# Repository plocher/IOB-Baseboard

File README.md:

# IOB-Baseboard
## License: CERN Open Hardware Licence v1.2

IOB Baseboard - wiring termination and I2C / Power bus management

The latest in the evolution of the perfect layout I/O system...
Previous I2C-xxx designs either let to a proliferation of adapters
(current sink, input filters...) and to less than robust mechanical
designs (daughtercards that easily pulled out of their sockets with
cable movement)

This version does 4 things:
 * All wiring is terminated into mechanically stable connection points
 * There are personality adapters to account for the level shifting, buffering and other I/O line adaptions that may be needed
 * While I like having blinking LED lights on every I/O line for debugging, others do not - so there is now a plug-in LED monitor slot for each set of 4x I/O lines
 * A generic I2C Expander plug in footprint.

I have built several board variations for various different I2C
Expander chips to take advantage of unique addressing, I/O levels,
cost, etc - with the only thing changing between boards being the
chip related stuff.  Maintaining and stocking several "slightly
different" board designs gets expensive, both from both inventory
and support perspectives.

V1.0 is a prototype that seeks to validate the basic modular assumptions I'm making.

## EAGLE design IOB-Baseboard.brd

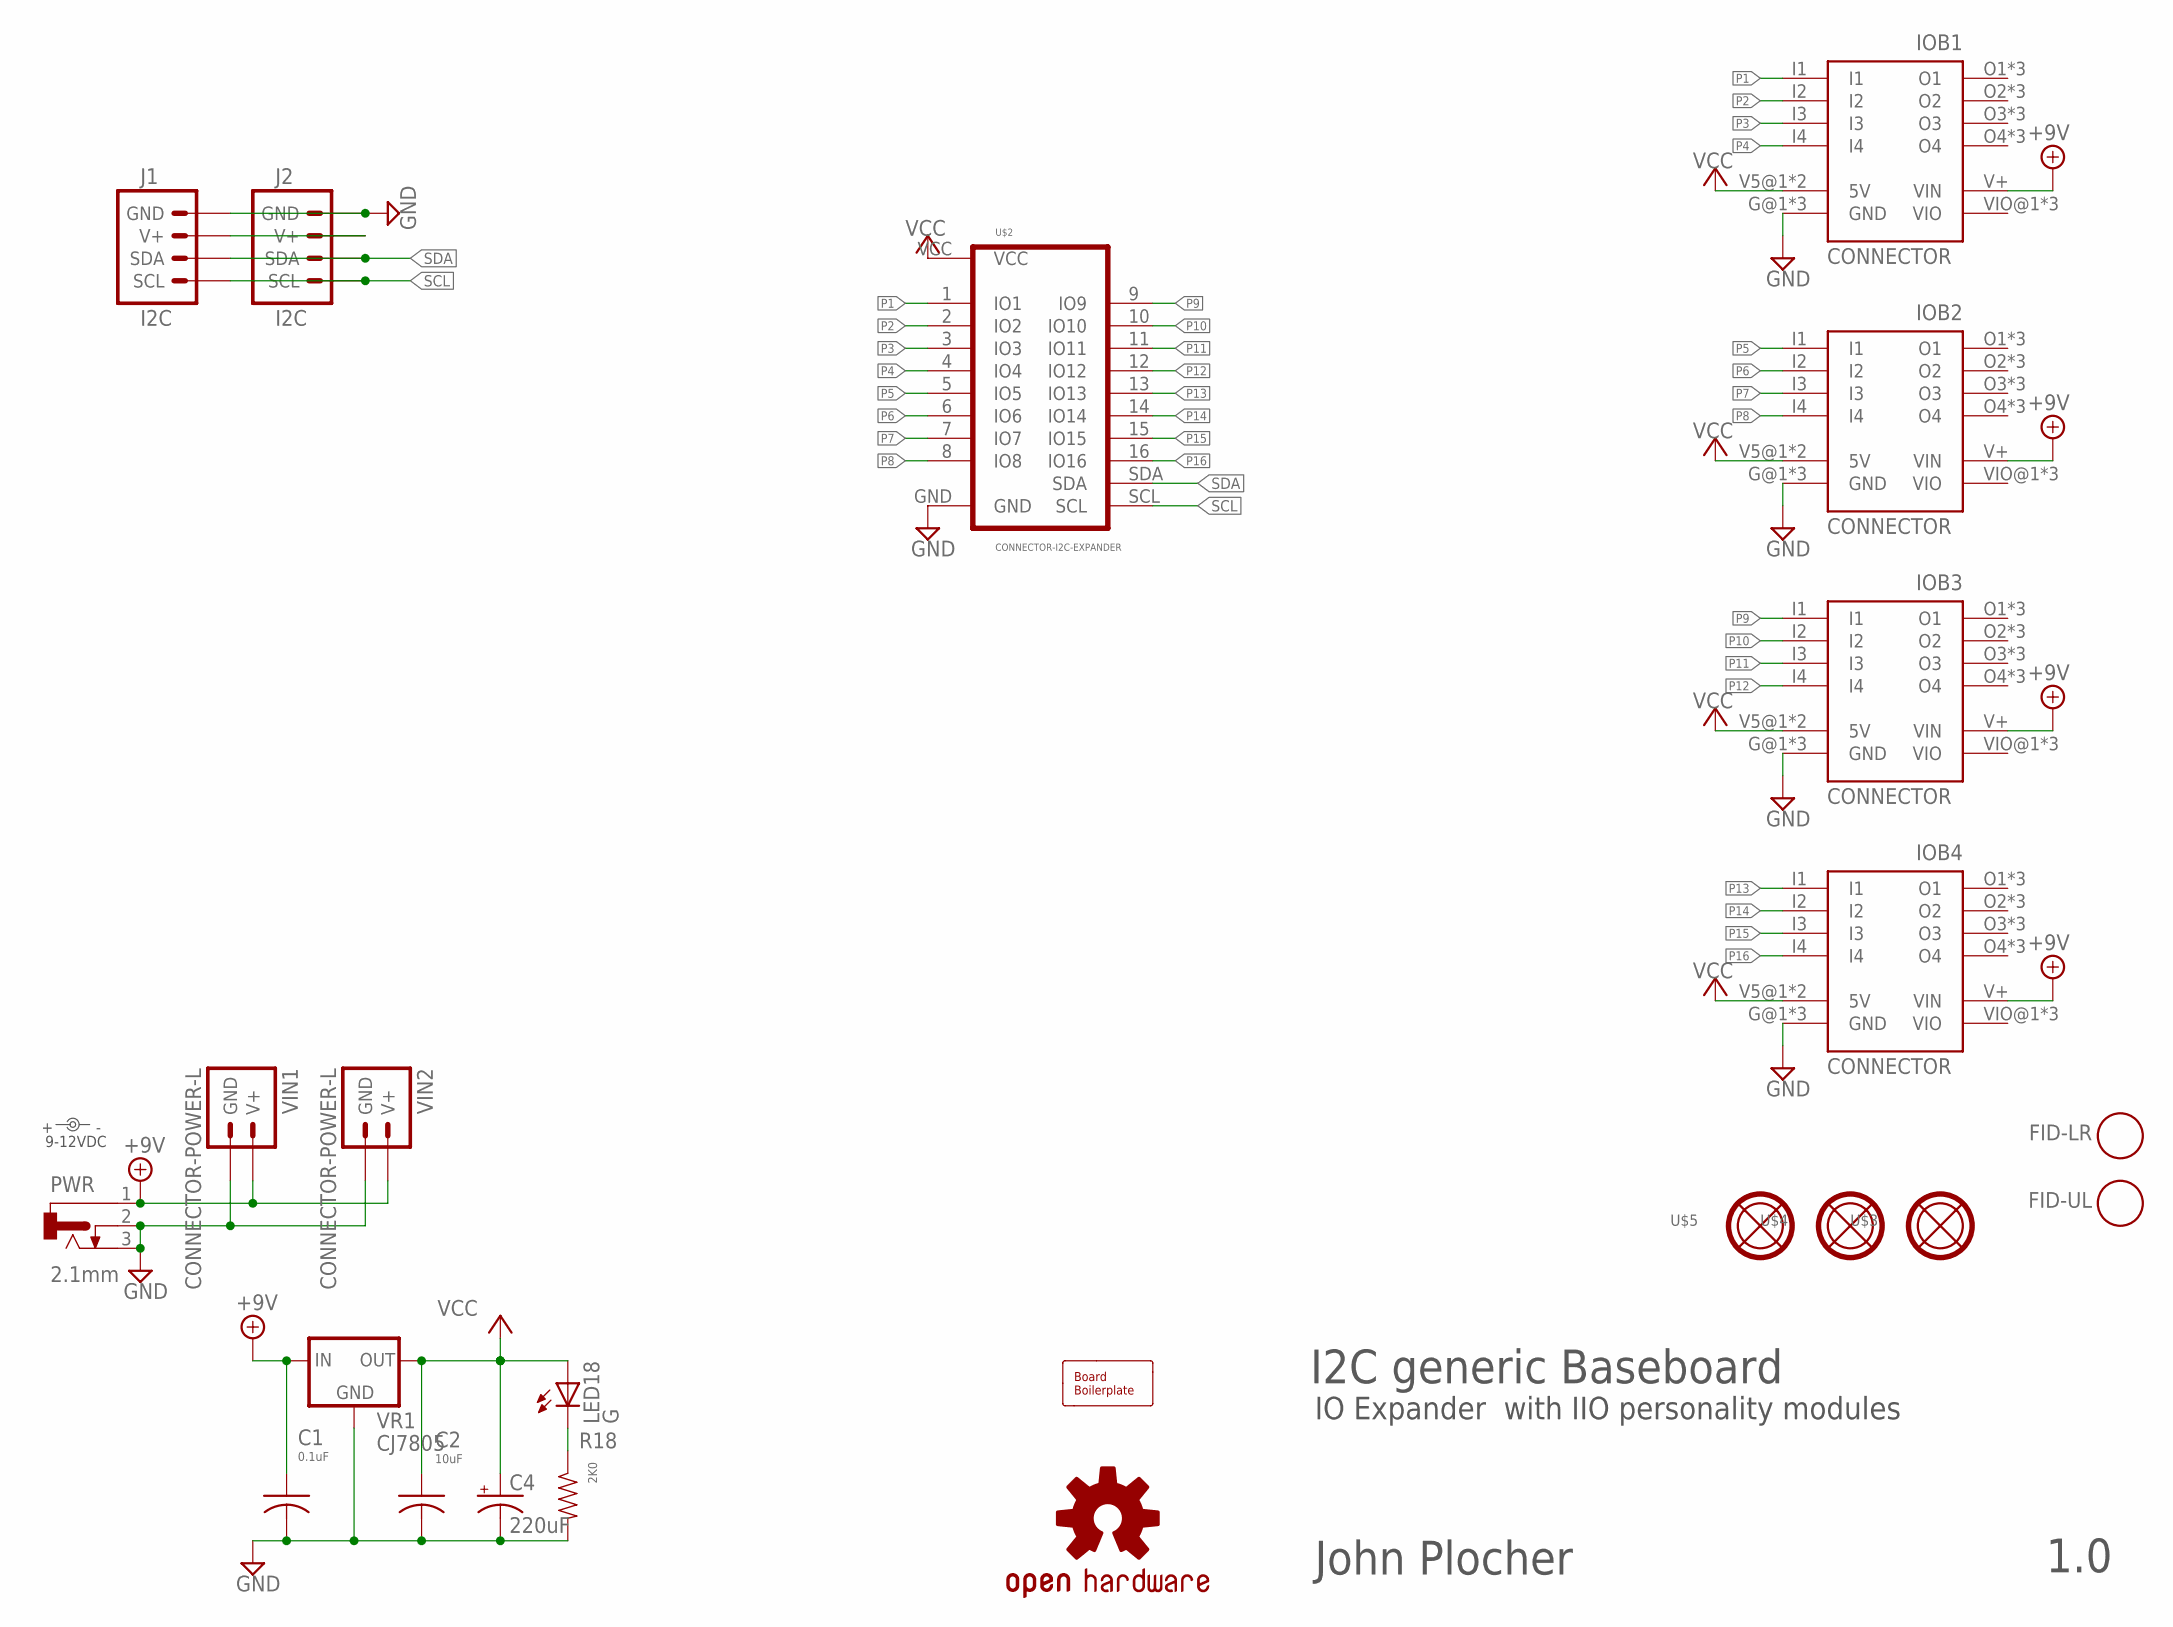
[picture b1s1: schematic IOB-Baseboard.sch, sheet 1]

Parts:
BOARD1: BOARD; BOARD-DINRAIL-3.17IN-IOB
C1: 0.1uF; 0603-CAP
C2: 10uF; 0603-CAP
C4: 220uF; 0810-CAP
FID-LR: FIDUCIAL; FIDUCIAL_1MM
FID-UL: FIDUCIAL; FIDUCIAL_1MM
IOB1, IOB2, IOB3, IOB4: CONNECTOR; IOB-V3-BASE
J1, J2: I2C; I2C-L
LED18: G; 0603-LED
PWR: 2.1mm; DCJ0202
R18: 2K0; 0603-RES
U$1: OSHW; OSHW-LOGO-L
U$2: CONNECTOR-I2C-EXPANDER; I2C-EXPANDER
U$3, U$4, U$5: MOUNTINGHOLE
VIN: 9-12VDC; PWR_LABEL
VIN1, VIN2: CONNECTOR-POWER-L; POWER-R2
VR1: CJ7805; TO-252

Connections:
GND: C1.2, C2.2, C4.-, IOB1.G@1 (GND), IOB1.G@2 (GND), IOB1.GND@3 (GND), IOB2.G@1 (GND), IOB2.G@2 (GND), IOB2.GND@3 (GND), IOB3.G@1 (GND), IOB3.G@2 (GND), IOB3.GND@3 (GND), IOB4.G@1 (GND), IOB4.G@2 (GND), IOB4.GND@3 (GND), J1.GND, J1.GND@1 (GND), J2.GND, J2.GND@1 (GND), PWR.2, PWR.3, R18.2, U$2.GND, VIN1.GND, VIN1.GND@1 (GND), VIN1.GND@2 (GND), VIN1.GND@3 (GND), VIN2.GND, VIN2.GND@1 (GND), VIN2.GND@2 (GND), VIN2.GND@3 (GND), VR1.2 (GND); also elsewhere on the board
unnamed: LED18.C, R18.1
P1: IOB1.I1, U$2.1 (IO1); also elsewhere on the board
P2: IOB1.I2, U$2.2 (IO2); also elsewhere on the board
P3: IOB1.I3, U$2.3 (IO3); also elsewhere on the board
P4: IOB1.I4, U$2.4 (IO4); also elsewhere on the board
P5: IOB2.I1, U$2.5 (IO5); also elsewhere on the board
P6: IOB2.I2, U$2.6 (IO6); also elsewhere on the board
P7: IOB2.I3, U$2.7 (IO7); also elsewhere on the board
P8: IOB2.I4, U$2.8 (IO8); also elsewhere on the board
P9: IOB3.I1, U$2.9 (IO9); also elsewhere on the board
P10: IOB3.I2, U$2.10 (IO10); also elsewhere on the board
P11: IOB3.I3, U$2.11 (IO11); also elsewhere on the board
P12: IOB3.I4, U$2.12 (IO12); also elsewhere on the board
P13: IOB4.I1, U$2.13 (IO13); also elsewhere on the board
P14: IOB4.I2, U$2.14 (IO14); also elsewhere on the board
P15: IOB4.I3, U$2.15 (IO15); also elsewhere on the board
P16: IOB4.I4, U$2.16 (IO16); also elsewhere on the board
SCL: J1.SCL, J1.SCL@1 (SCL), J2.SCL, J2.SCL@1 (SCL), U$2.SCL
SDA: J1.SDA, J1.SDA@1 (SDA), J2.SDA, J2.SDA@1 (SDA), U$2.SDA
V+I2C: J1.V+, J1.V+@1 (V+), J2.V+, J2.V+@1 (V+)
VCC: C2.1, C4.+, IOB1.V5@1 (5V), IOB1.V5@2 (5V), IOB2.V5@1 (5V), IOB2.V5@2 (5V), IOB3.V5@1 (5V), IOB3.V5@2 (5V), IOB4.V5@1 (5V), IOB4.V5@2 (5V), LED18.A, U$2.VCC, VR1.3 (OUT); also elsewhere on the board
VIN: C1.1, IOB1.V+ (VIN), IOB2.V+ (VIN), IOB3.V+ (VIN), IOB4.V+ (VIN), PWR.1, VIN1.V+, VIN1.V+@1 (V+), VIN1.V+@2 (V+), VIN1.V+@3 (V+), VIN2.V+, VIN2.V+@1 (V+), VIN2.V+@2 (V+), VIN2.V+@3 (V+), VR1.1 (IN)

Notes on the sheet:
I2C generic Baseboard
IO Expander with IIO personality modules
John Plocher
1.0

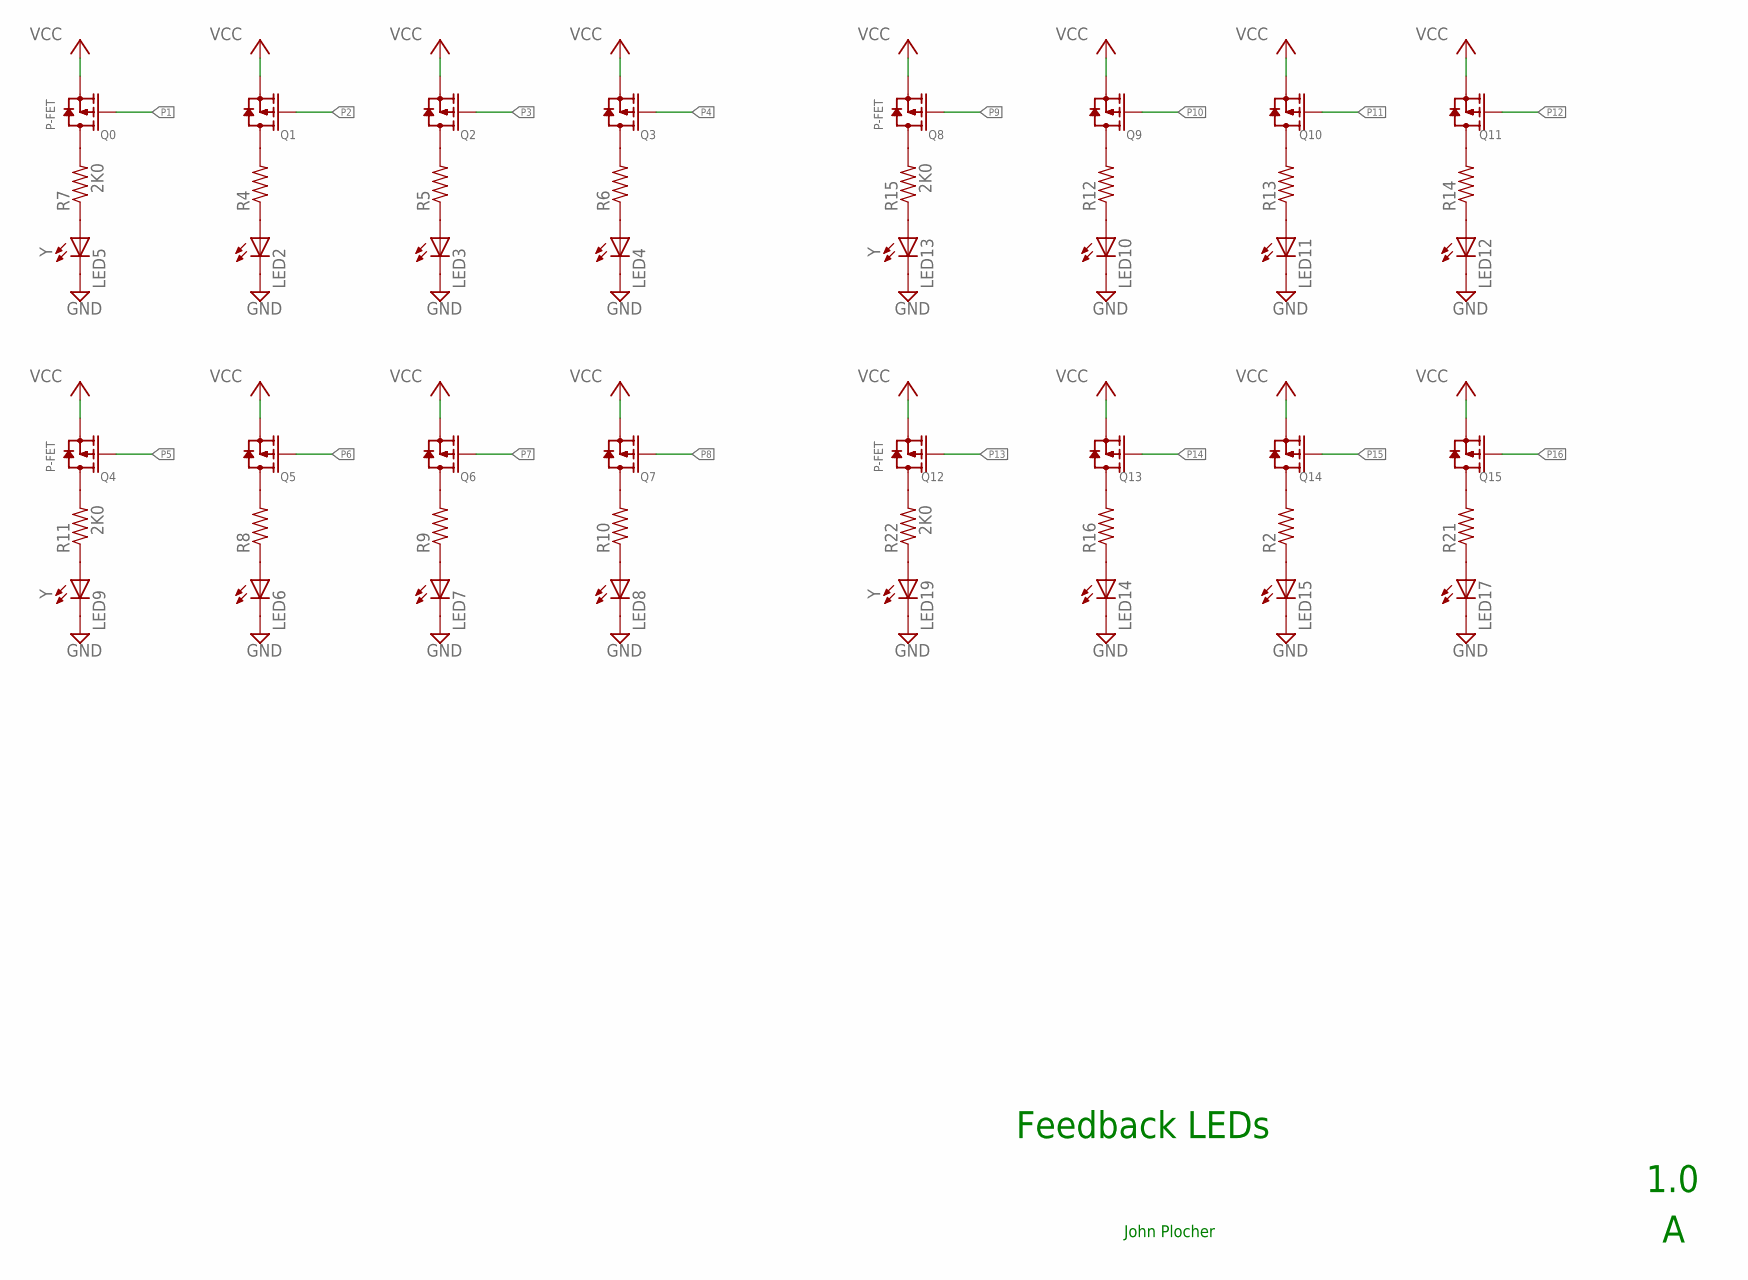
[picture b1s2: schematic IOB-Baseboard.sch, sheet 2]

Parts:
LED2, LED3, LED4, LED5, LED6, LED7, LED8, LED9, LED10, LED11, LED12, LED13, LED14, LED15, LED17, LED19: Y; 0603-LED
Q0, Q1, Q2, Q3, Q4, Q5, Q6, Q7, Q8, Q9, Q10, Q11, Q12, Q13, Q14, Q15: P-FET; SOT23
R2, R4, R5, R6, R7, R8, R9, R10, R11, R12, R13, R14, R15, R16, R21, R22: 2K0; 0603-RES

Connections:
GND: LED2.C, LED3.C, LED4.C, LED5.C, LED6.C, LED7.C, LED8.C, LED9.C, LED10.C, LED11.C, LED12.C, LED13.C, LED14.C, LED15.C, LED17.C, LED19.C; also elsewhere on the board
unnamed: Q4.3 (D), R11.2
unnamed: Q5.3 (D), R8.2
unnamed: Q6.3 (D), R9.2
unnamed: Q7.3 (D), R10.2
unnamed: LED9.A, R11.1
unnamed: LED6.A, R8.1
unnamed: LED7.A, R9.1
unnamed: LED8.A, R10.1
unnamed: Q8.3 (D), R15.2
unnamed: Q9.3 (D), R12.2
unnamed: Q10.3 (D), R13.2
unnamed: Q11.3 (D), R14.2
unnamed: LED13.A, R15.1
unnamed: LED10.A, R12.1
unnamed: LED11.A, R13.1
unnamed: LED12.A, R14.1
unnamed: Q12.3 (D), R22.2
unnamed: Q13.3 (D), R16.2
unnamed: Q14.3 (D), R2.2
unnamed: Q15.3 (D), R21.2
unnamed: LED19.A, R22.1
unnamed: LED14.A, R16.1
unnamed: LED15.A, R2.1
unnamed: LED17.A, R21.1
unnamed: Q0.3 (D), R7.2
unnamed: Q1.3 (D), R4.2
unnamed: Q2.3 (D), R5.2
unnamed: Q3.3 (D), R6.2
unnamed: LED5.A, R7.1
unnamed: LED2.A, R4.1
unnamed: LED3.A, R5.1
unnamed: LED4.A, R6.1
P1: Q0.1 (G); also elsewhere on the board
P2: Q1.1 (G); also elsewhere on the board
P3: Q2.1 (G); also elsewhere on the board
P4: Q3.1 (G); also elsewhere on the board
P5: Q4.1 (G); also elsewhere on the board
P6: Q5.1 (G); also elsewhere on the board
P7: Q6.1 (G); also elsewhere on the board
P8: Q7.1 (G); also elsewhere on the board
P9: Q8.1 (G); also elsewhere on the board
P10: Q9.1 (G); also elsewhere on the board
P11: Q10.1 (G); also elsewhere on the board
P12: Q11.1 (G); also elsewhere on the board
P13: Q12.1 (G); also elsewhere on the board
P14: Q13.1 (G); also elsewhere on the board
P15: Q14.1 (G); also elsewhere on the board
P16: Q15.1 (G); also elsewhere on the board
VCC: Q0.2 (S), Q1.2 (S), Q2.2 (S), Q3.2 (S), Q4.2 (S), Q5.2 (S), Q6.2 (S), Q7.2 (S), Q8.2 (S), Q9.2 (S), Q10.2 (S), Q11.2 (S), Q12.2 (S), Q13.2 (S), Q14.2 (S), Q15.2 (S); also elsewhere on the board

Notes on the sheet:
Feedback LEDs
1.0
John Plocher

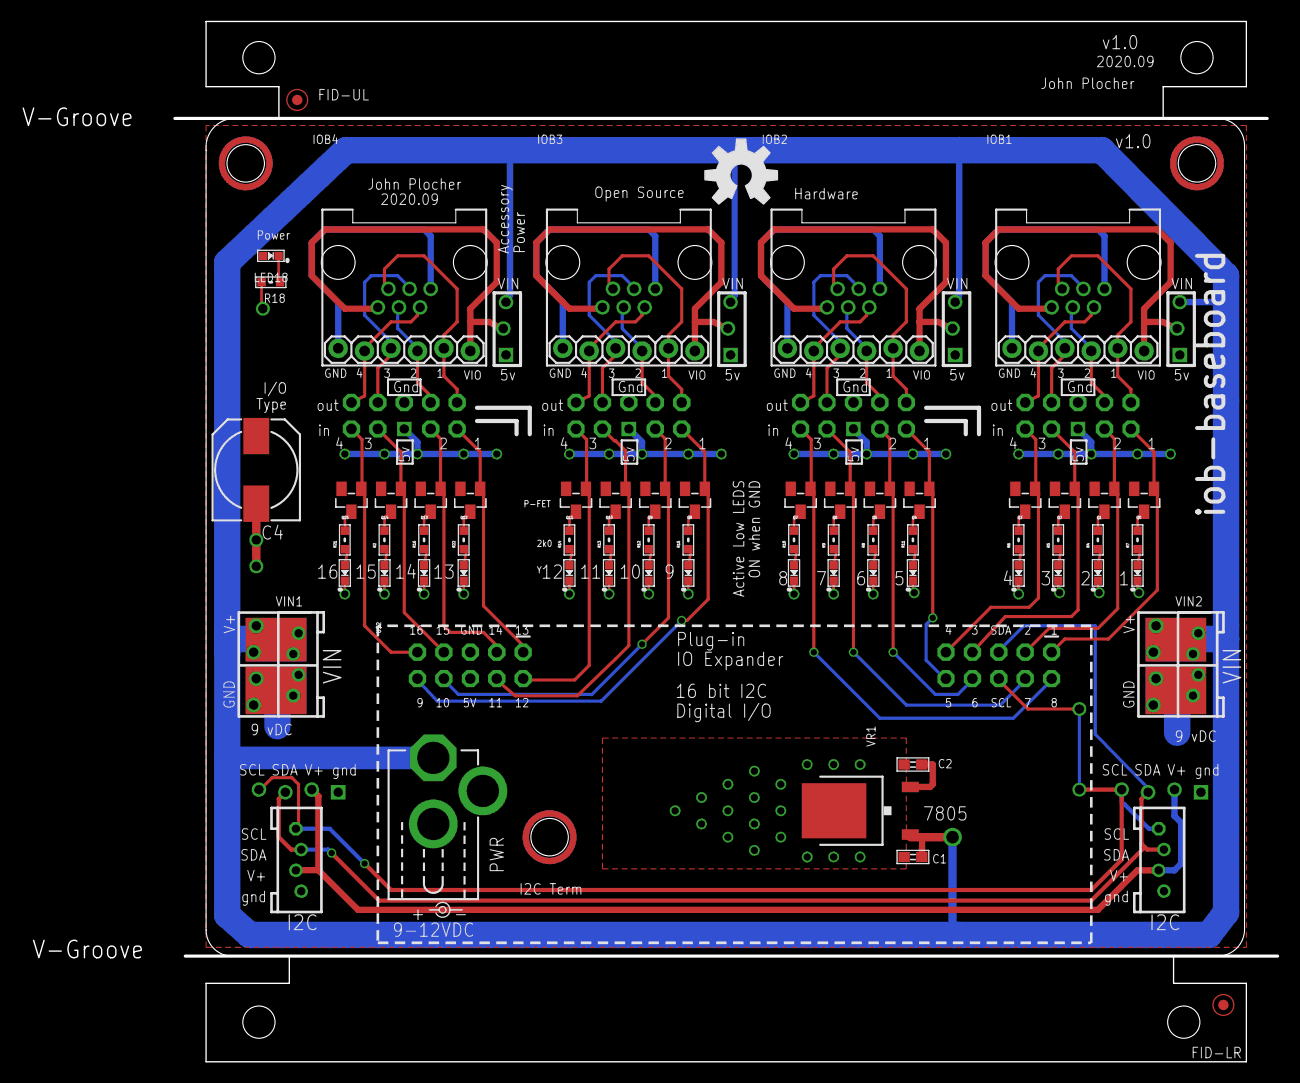
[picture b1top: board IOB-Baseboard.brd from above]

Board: 2 copper layers, 120.7 x 99.8 mm, 72 parts (0 on the bottom side), 55 nets.

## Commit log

2020-09-04 Initial version
2020-09-05 fixed silk, added graphic
2020-09-05 added graphic
2020-09-05 added mounting holes
2020-09-11 put LEDS back on board, move 2x5 personal;ity and VIO connectors
2020-09-11 update version text
2020-09-11 update docs
2020-10-05 added values for connectors
2020-10-06 normalized values
